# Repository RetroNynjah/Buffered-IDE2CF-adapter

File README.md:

# Buffered IDE2CF Adapter
<br/>
This adapter was designed with the TF1260 accelerator board in mind because my TF1260 EHIDE interface does not work with a plain IDE2CF-adapter but works fine with a buffered adapter.  
The shape of the adapter makes it fit directly on top of the Tf1260 even if there are heatsinks on the CPLDs.  
It can also be fitted onto the standard IDE controller on the motherboard of the Amiga 1200 but there's not enough room to fit it directly onto the motherboard of the Amiga 600.  
When used with the onboard IDE controller on the Amiga 1200 it can cause issues with some RTC clock modules. This is not the case when used with the Terrible Fire boards that it was designed for.   

The adapter provides an external LED connector so that the Amiga 1200 HDD LED can be connected to the IDE2CF adapter instead of the motherboard and thereby making the standard HDD LED work with the TF1260 EHIDE interface.  
<br/>

### Build & configuration
The adapter is designed to have a 44-pin female IDE-connector on the bottom side which can mate directly to the IDE controller's pin header.  
If you wish to connect the adapter to an IDE cable, use a 44-pin male pin header on the top side of the adapter instead.

#### External LED connector
The external LED connector has two pins. Pin 1 which is the right pin (square pad) is active low and the pin 2 which is the left PIN is the inverted version of pin 1.
You can connect just on of the pins to an LED if the LED is connected to either ground or +5V (or similar).  
Depending on if the LED you are connecting has a current limiting resistor, you may or may not need to add a resistor on the adapter. That is either R3 or R4. On the pins where you don't need resistors, simply add a solder blob to close the corresponding jumper (JP3 or JP4)
You can also connect an LED across both pins. If you do, add one resistor to either of the pins and add a solder blob to the jumper for the other pin.
JP4/R4 is for pin 1  
JP3/R3 is for pin 2  

Some LED configurations examples:

##### Amiga 1200 HDD LED on original LED board (with resistor)
* Unplug LED cable from motherboard connector
* Connect LED cable to pin 2 (left pin)
* Add solder to JP3 (there is already a resistor on the LED board)
* R4/JP4 can be left unpopulated as they aren't used.

##### External LED connected to ground
* Connect LED to pin 2 (left)  
* Do NOT add solder to JP3
* Add a current limiting resitor to R3. 560 Ohm is probably a good value.  
* R4/JP4 can be left unpopulated as they aren't used.

##### External LED connected to +5V
* Connect LED to pin 1 (right)  
* Do NOT add solder to JP4.  
* Add a current limiting resitor to R4. 560 Ohm is probably a good value.  
* R3/JP3 can be left unpopulated as they aren't used.

##### External LED connected only to pin 1 and 2.
* Connect LED anode to pin 2 (left) and cathode to pin 1 (right)  
* Do NOT add solder to JP3.  
* Add solder to JP4
* Add a current limiting resitor to R3. 560 Ohm is probably a good value.  

#### U4 LED buffer
The optional U4 is optional.
If you wish to leave U4 out and drive the LEDs directly from the CF card, you need to close jumper JP2 to let the signal pass by the unpopulated U4 footprint.

#### Master/Slave
The jumpers JP1.1 and JP1.2 are used for setting master/slave configuration. JP1.1 is bridged by default and configures the drive as master.  
If you wish to use the drive in a slave configuration you should cut JP1.1 and optionally install a master/slave jumper at JP1.2 or add a solder blob at JP1.1 when you want to set the drive as master again.
If JP1.1 is uncut or closed with a solder blob, JP1.2 has no effect at at.

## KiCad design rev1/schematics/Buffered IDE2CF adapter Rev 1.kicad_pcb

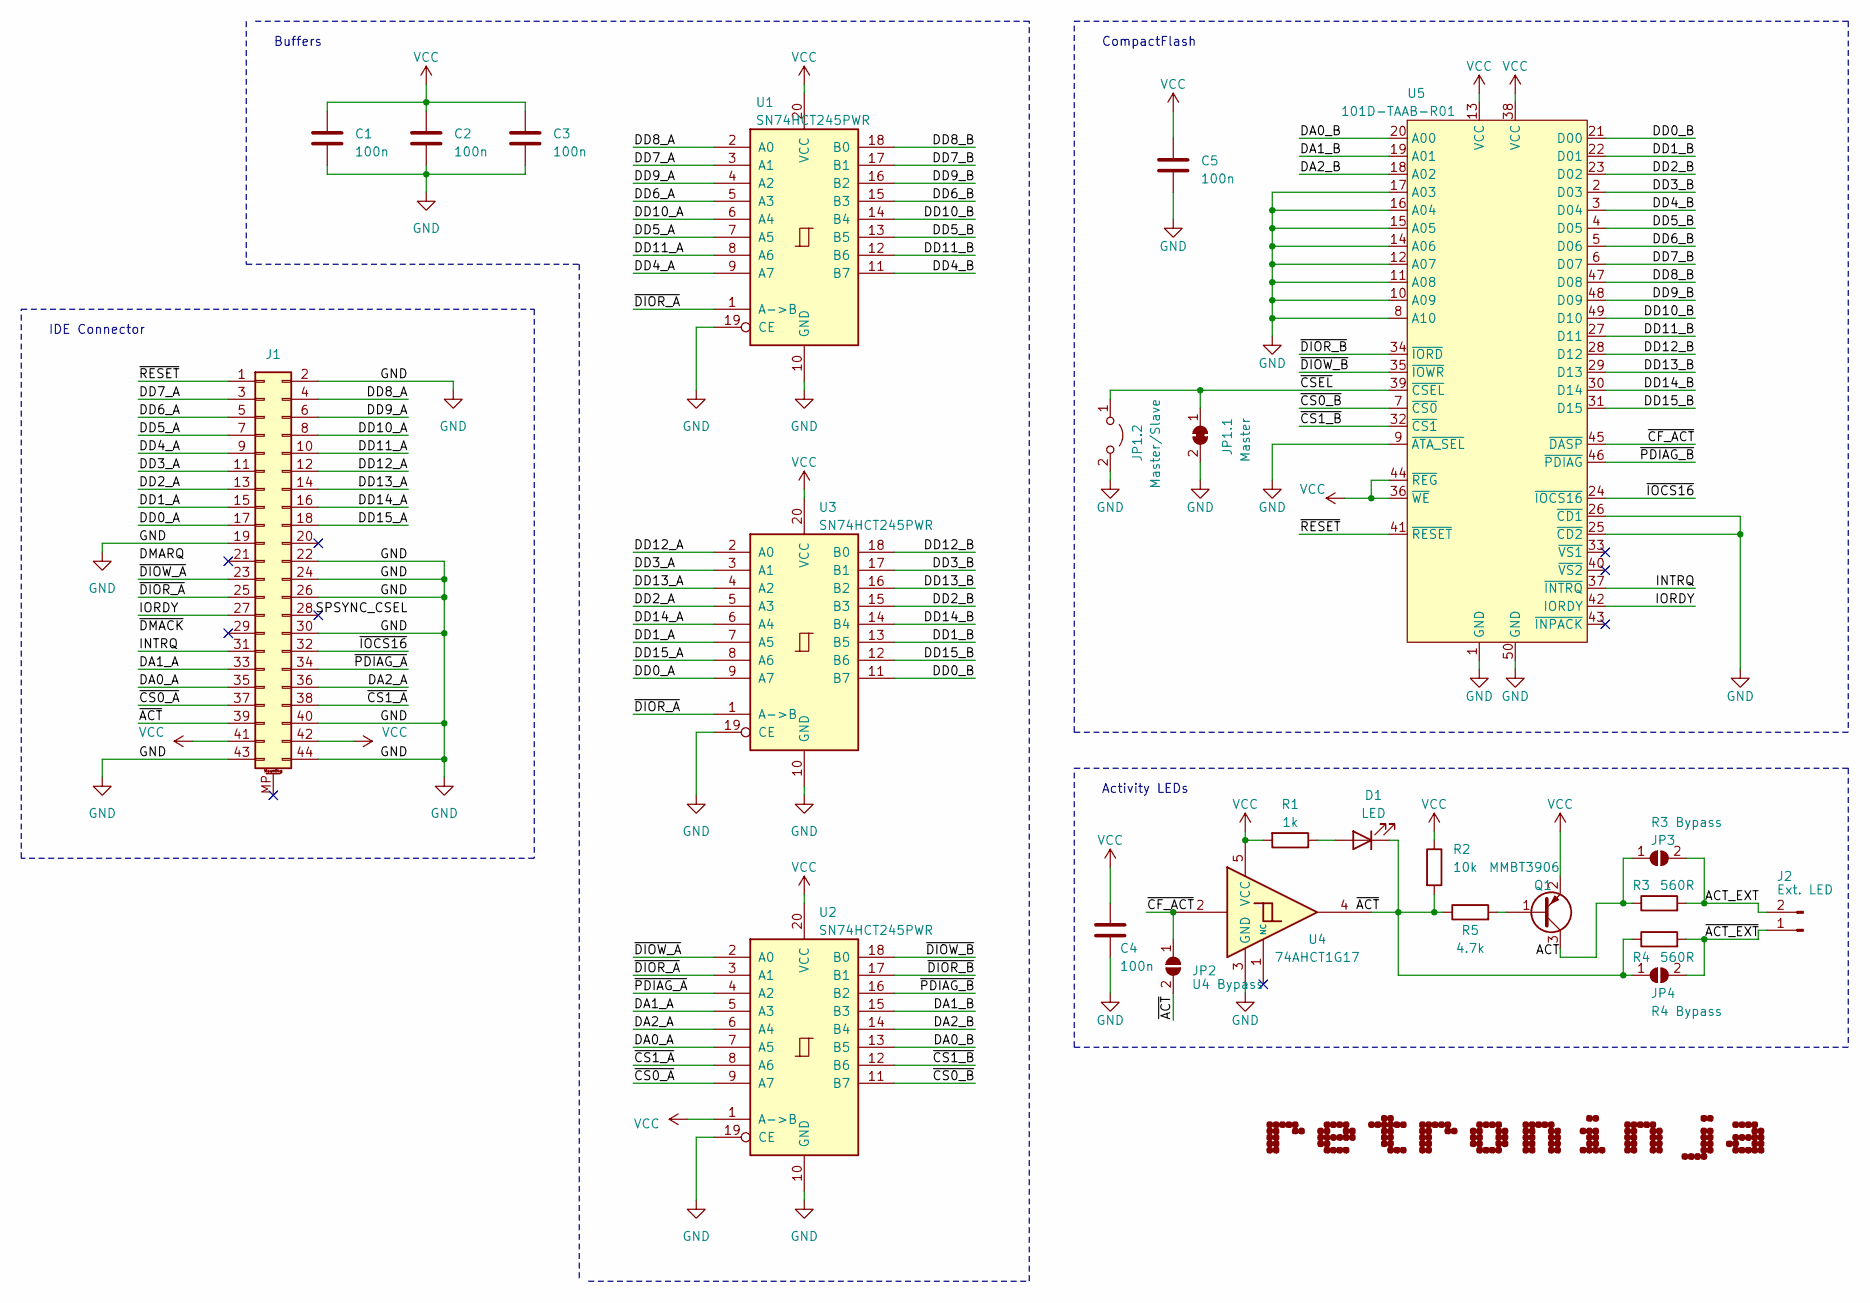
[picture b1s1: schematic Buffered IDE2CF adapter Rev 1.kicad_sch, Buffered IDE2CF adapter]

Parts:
C1, C2, C3, C4, C5: 100n; C_0603_1608Metric_Pad1.08x0.95mm_HandSolder
D1: LED; LED_0805_2012Metric_Pad1.15x1.40mm_HandSolder
J1: IDE Connector; PinHeader_2x22_P2.00mm_Vertical
J2: Ext. LED; PinHeader_1x02_P2.54mm_Vertical
JP1.1: Master; SolderJumper-2_P1.3mm_Bridged_RoundedPad1.0x1.5mm
JP1.2: Master/Slave; PinHeader_1x02_P2.54mm_Vertical
JP2: U4 Bypass; SolderJumper-2_P1.3mm_Open_RoundedPad1.0x1.5mm
JP3: R3 Bypass; SolderJumper-2_P1.3mm_Open_RoundedPad1.0x1.5mm
JP4: R4 Bypass; SolderJumper-2_P1.3mm_Open_RoundedPad1.0x1.5mm
Q1: MMBT3906; SOT-23
R1: 1k; R_0603_1608Metric_Pad0.98x0.95mm_HandSolder
R2: 10k; R_0603_1608Metric_Pad0.98x0.95mm_HandSolder
R3, R4: 560R; R_0603_1608Metric_Pad0.98x0.95mm_HandSolder
R5: 4.7k; R_0603_1608Metric_Pad0.98x0.95mm_HandSolder
U1, U2, U3: SN74HCT245PWR; TSSOP-20_4.4x6.5mm_P0.65mm
U4: 74AHCT1G17; SOT-23-5_HandSoldering
U5: 101D-TAAB-R01; 101DTAABR01

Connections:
/ACT: JP3.1 (A), Q1.3 (C), R3.1
/ACT_EXT: J2.2, JP3.2 (B), R3.2
/DA0_A: J1.35, U2.7 (A5)
/DA0_B: U2.13 (B5), U5.20 (A00)
/DA1_A: J1.33, U2.5 (A3)
/DA1_B: U2.15 (B3), U5.19 (A01)
/DA2_A: J1.36, U2.6 (A4)
/DA2_B: U2.14 (B4), U5.18 (A02)
/DD0_A: J1.17, U3.9 (A7)
/DD0_B: U3.11 (B7), U5.21 (D00)
/DD1_A: J1.15, U3.7 (A5)
/DD1_B: U3.13 (B5), U5.22 (D01)
/DD2_A: J1.13, U3.5 (A3)
/DD2_B: U3.15 (B3), U5.23 (D02)
/DD3_A: J1.11, U3.3 (A1)
/DD3_B: U3.17 (B1), U5.2 (D03)
/DD4_A: J1.9, U1.9 (A7)
/DD4_B: U1.11 (B7), U5.3 (D04)
/DD5_A: J1.7, U1.7 (A5)
/DD5_B: U1.13 (B5), U5.4 (D05)
/DD6_A: J1.5, U1.5 (A3)
/DD6_B: U1.15 (B3), U5.5 (D06)
/DD7_A: J1.3, U1.3 (A1)
/DD7_B: U1.17 (B1), U5.6 (D07)
/DD8_A: J1.4, U1.2 (A0)
/DD8_B: U1.18 (B0), U5.47 (D08)
/DD9_A: J1.6, U1.4 (A2)
/DD9_B: U1.16 (B2), U5.48 (D09)
/DD10_A: J1.8, U1.6 (A4)
/DD10_B: U1.14 (B4), U5.49 (D10)
/DD11_A: J1.10, U1.8 (A6)
/DD11_B: U1.12 (B6), U5.27 (D11)
/DD12_A: J1.12, U3.2 (A0)
/DD12_B: U3.18 (B0), U5.28 (D12)
/DD13_A: J1.14, U3.4 (A2)
/DD13_B: U3.16 (B2), U5.29 (D13)
/DD14_A: J1.16, U3.6 (A4)
/DD14_B: U3.14 (B4), U5.30 (D14)
/DD15_A: J1.18, U3.8 (A6)
/DD15_B: U3.12 (B6), U5.31 (D15)
/INTRQ: J1.31, U5.37 (~INTRQ)
/IORDY: J1.27, U5.42 (IORDY)
/~ACT_EXT: J2.1, JP4.2 (B), R4.2
/~ACT: D1.1 (K), J1.39, JP2.2 (B), JP4.1 (A), R2.2, R4.1, R5.1, U4.4
/~CF_ACT: JP2.1 (A), U4.2, U5.45 (~DASP)
/~CS0_A: J1.37, U2.9 (A7)
/~CS0_B: U2.11 (B7), U5.7 (~CS0)
/~CS1_A: J1.38, U2.8 (A6)
/~CS1_B: U2.12 (B6), U5.32 (~CS1)
/~CSEL: JP1.1.1 (A), JP1.2.1 (A), U5.39 (~CSEL)
/~DIOR_A: J1.25, U1.1 (A->B), U2.3 (A1), U3.1 (A->B)
/~DIOR_B: U2.17 (B1), U5.34 (~IORD)
/~DIOW_A: J1.23, U2.2 (A0)
/~DIOW_B: U2.18 (B0), U5.35 (~IOWR)
/~IOCS16: J1.32, U5.24 (~IOCS16)
/~PDIAG_A: J1.34, U2.4 (A2)
/~PDIAG_B: U2.16 (B2), U5.46 (~PDIAG)
/~RESET: J1.1, U5.41 (~RESET)
GND: C1.2, C2.2, C3.2, C4.2, C5.2, J1.2, J1.19, J1.22, J1.24, J1.26, J1.30, J1.40, J1.43, J1.44, JP1.1.2 (B), JP1.2.2 (B), U1.10 (GND), U1.19 (CE), U2.10 (GND), U2.19 (CE), U3.10 (GND), U3.19 (CE), U4.3 (GND), U5.1 (GND), U5.8 (A10), U5.9 (~ATA_SEL), U5.10 (A09), U5.11 (A08), U5.12 (A07), U5.14 (A06), U5.15 (A05), U5.16 (A04), U5.17 (A03), U5.25 (~CD2), U5.26 (~CD1), U5.50 (GND)
unnamed: D1.2 (A), R1.1
unnamed: Q1.1 (B), R5.2
VCC: C1.1, C2.1, C3.1, C4.1, C5.1, J1.41, J1.42, Q1.2 (E), R1.2, R2.1, U1.20 (VCC), U2.1 (A->B), U2.20 (VCC), U3.20 (VCC), U4.5 (VCC), U5.13 (VCC), U5.36 (~WE), U5.38 (VCC), U5.44 (~REG)

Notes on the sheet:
Buffers
IDE Connector
Activity LEDs
CompactFlash

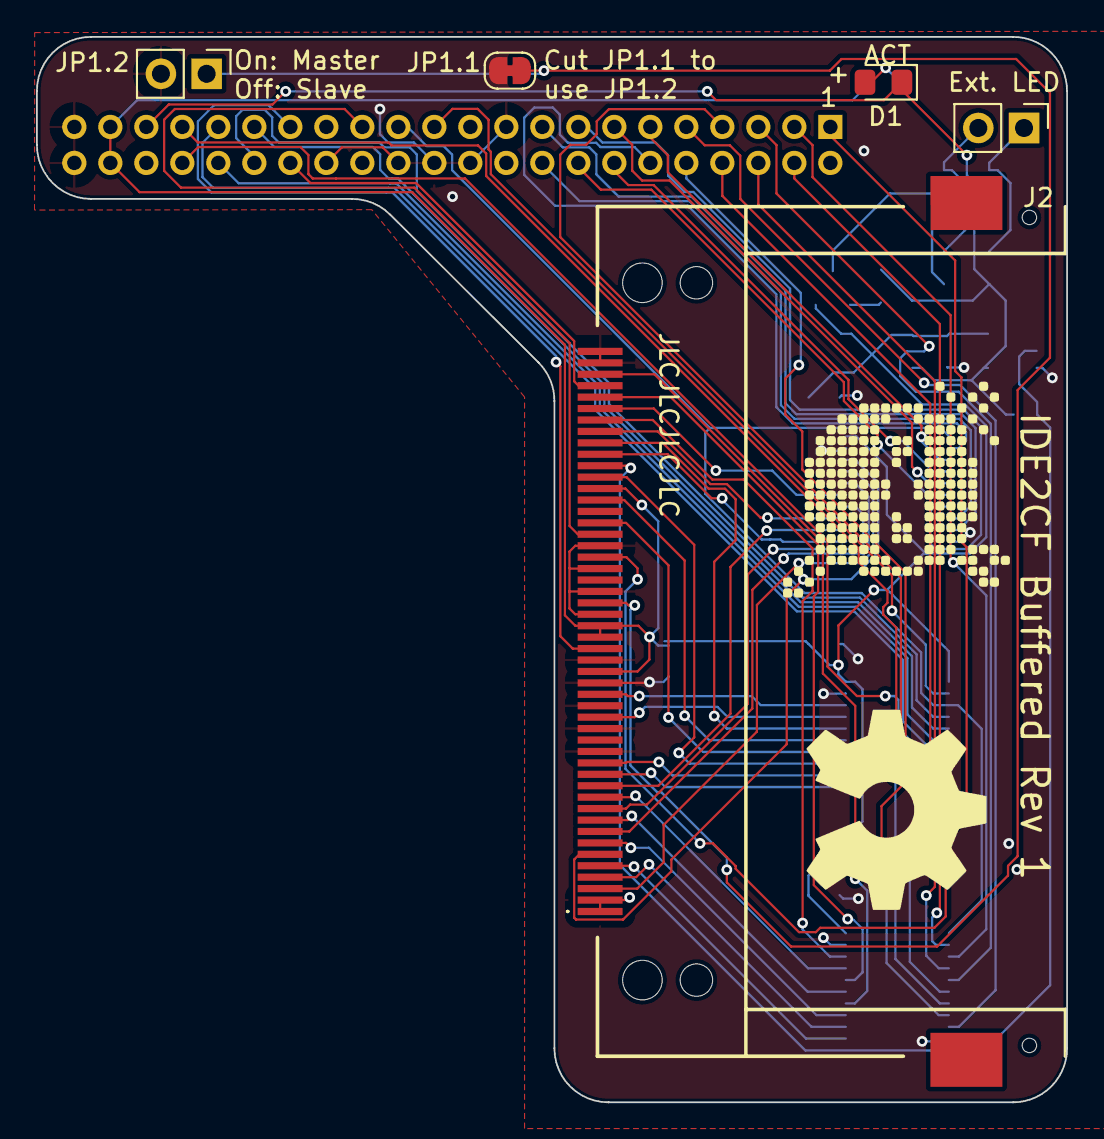
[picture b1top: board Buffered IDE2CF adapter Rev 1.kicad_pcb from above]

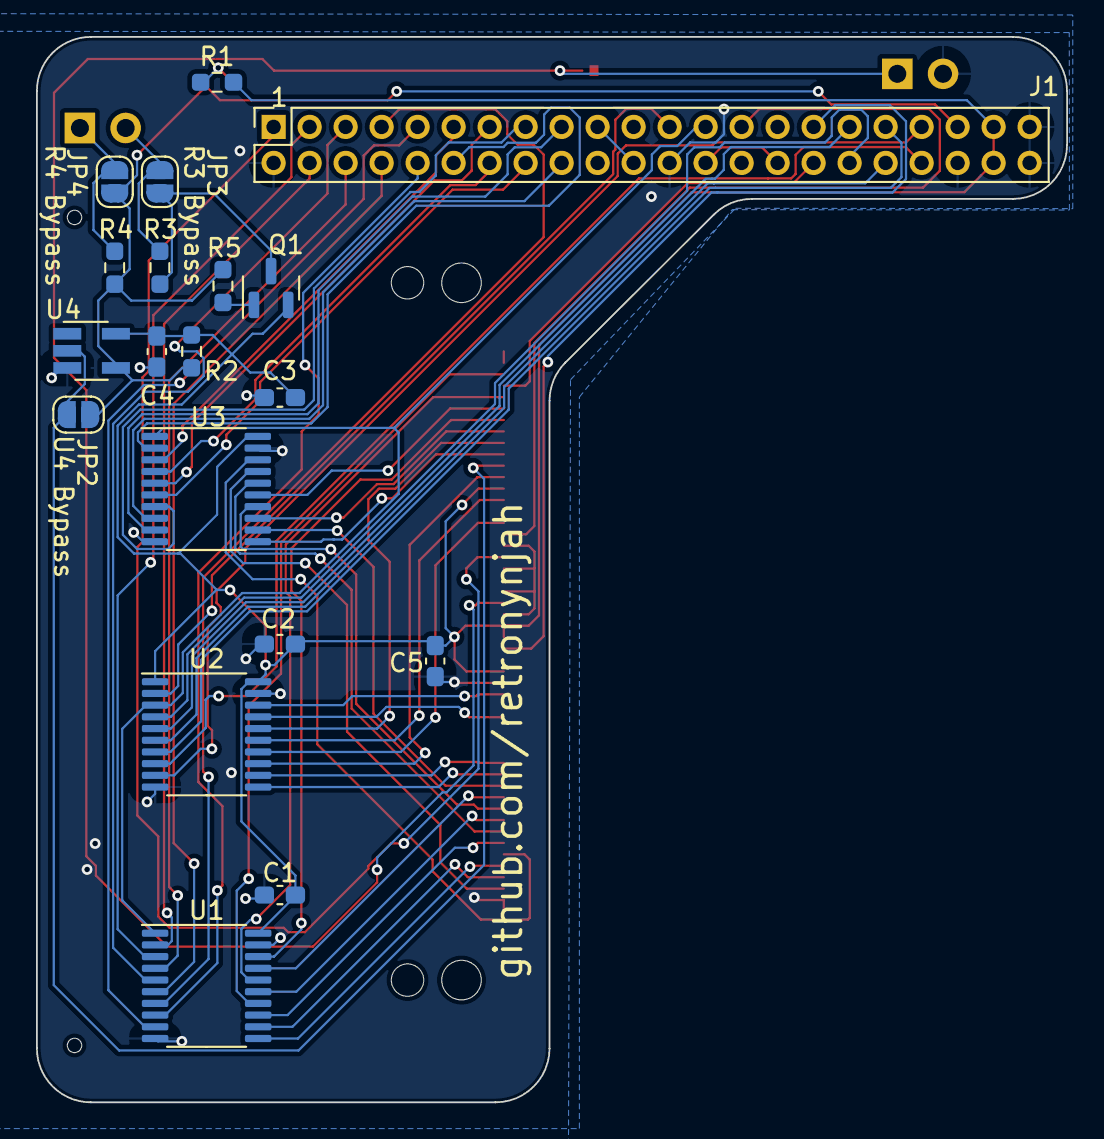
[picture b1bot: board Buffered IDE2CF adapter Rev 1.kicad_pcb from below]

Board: 2 copper layers, 57.2 x 59.2 mm, 26 parts (18 on the bottom side), 62 nets.

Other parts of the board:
OSHW: LOGO
retroninja: LOGO

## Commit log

2023-06-04 Initial upload
